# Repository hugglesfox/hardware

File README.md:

# Hardware

Random hardware design projects I have done. They probably don't work.

## Contents

- [obd2-pihat](https://github.com/hugglesfox/hardware/tree/master/obd2-pihat): An OBD-II hat for the raspberry pi.
- [fibonacci](https://github.com/hugglesfox/hardware/tree/master/fibonacci): A 4 bit fibonacci sequence calculator.

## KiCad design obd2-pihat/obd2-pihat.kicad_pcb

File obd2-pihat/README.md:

# OBD-II PiHAT

An OBD-II interface hat for the raspberry pi featuring the TI MCP2515 CAN
controller and a 12v to 5v power supply for backpowering the pi from the car
battery.

See the
[schematic](https://github.com/hugglesfox/hardware/blob/master/obd2-pihat/schematic.pdf)
for more details.

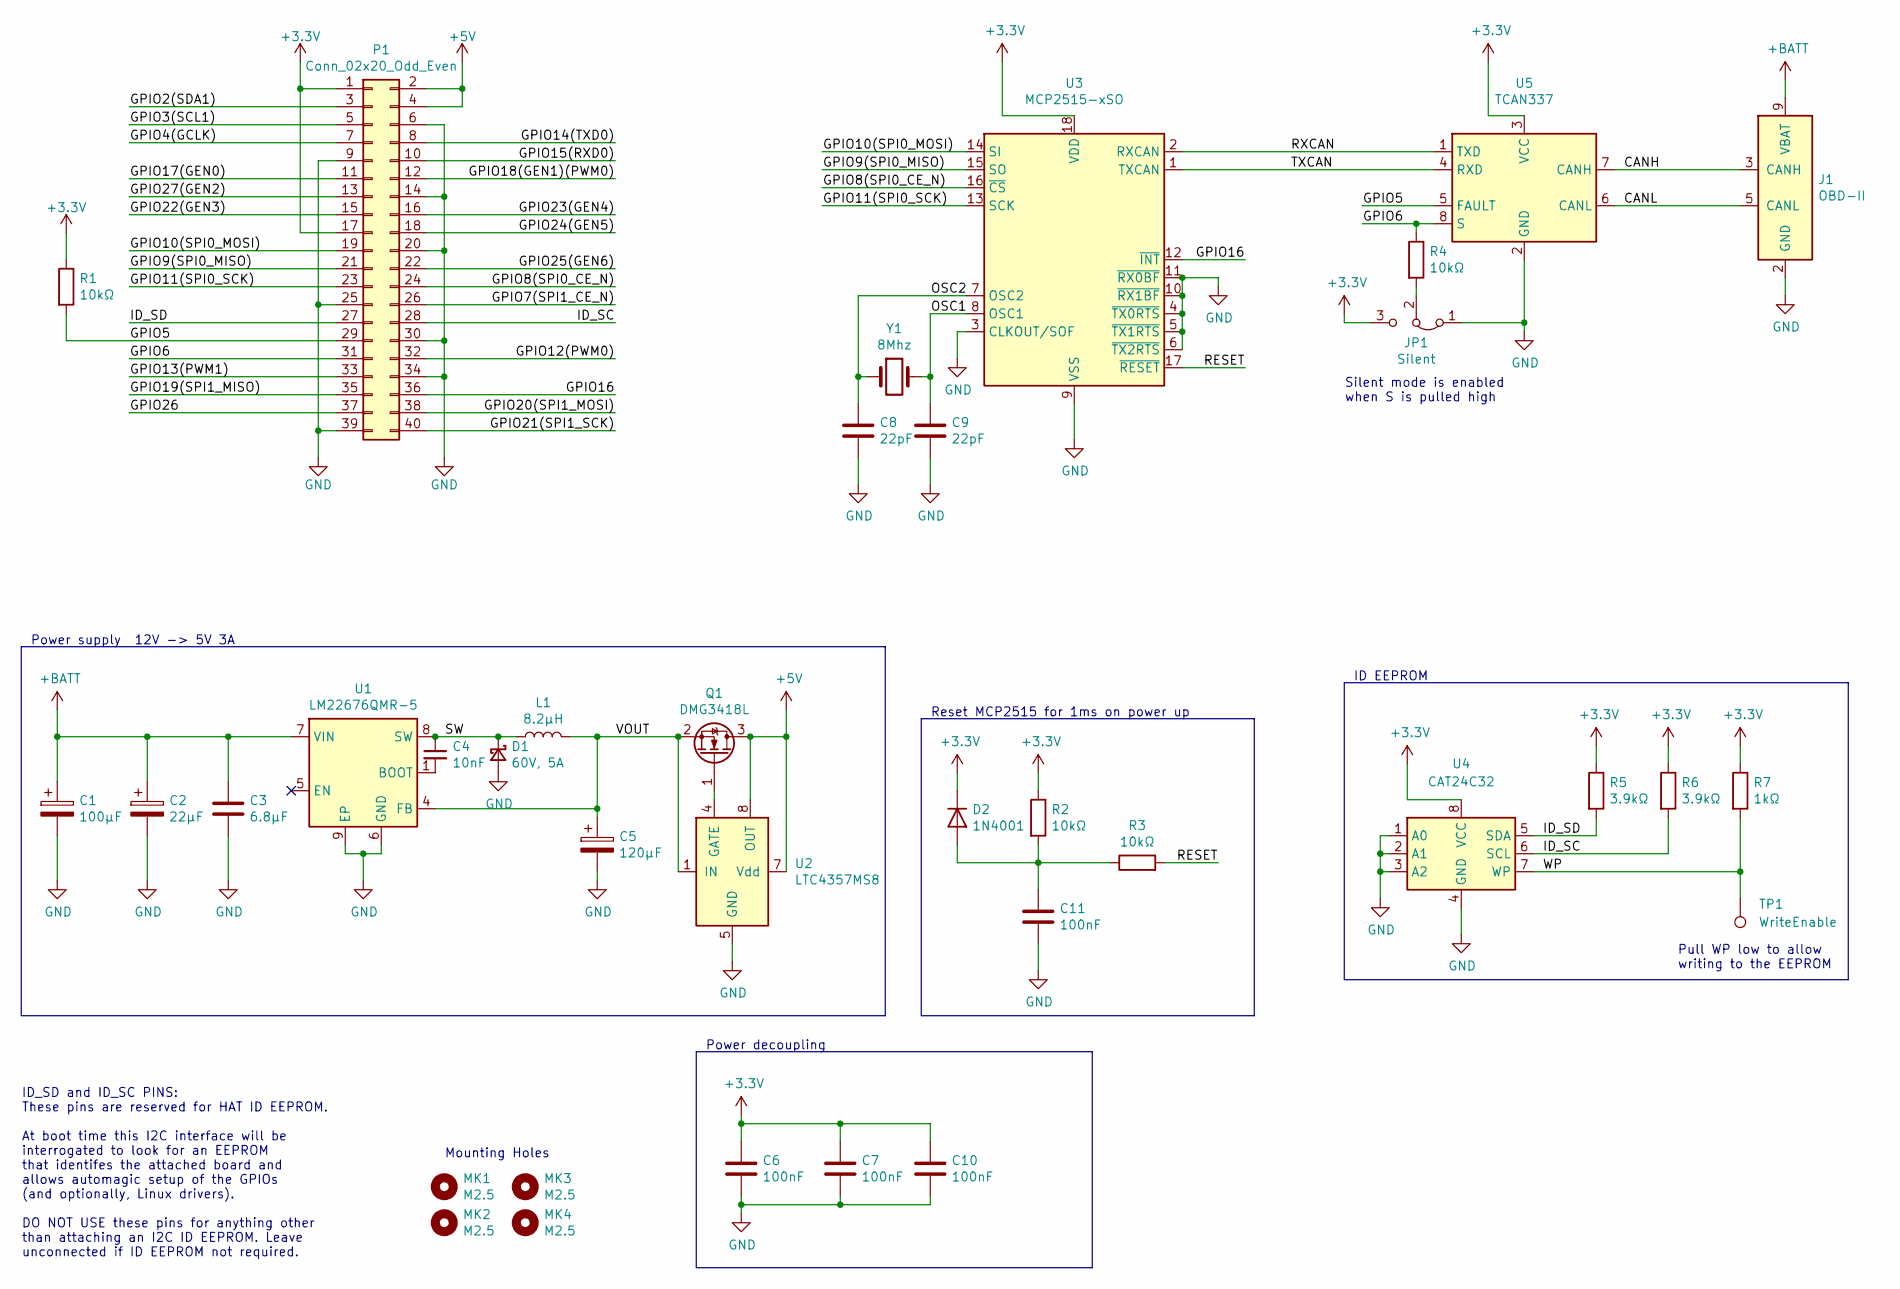
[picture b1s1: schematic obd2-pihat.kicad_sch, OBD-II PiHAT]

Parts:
C1: 100μF; CP_Elec_5x5.4
C2: 22μF; CP_Elec_4x5.4
C3: 6.8μF; C_0805_2012Metric_Pad1.18x1.45mm_HandSolder
C4: 10nF; C_0805_2012Metric_Pad1.18x1.45mm_HandSolder
C5: 120μF; CP_Elec_5x5.9
C6, C7, C10, C11: 100nF; C_0805_2012Metric_Pad1.18x1.45mm_HandSolder
C8, C9: 22pF; C_0805_2012Metric_Pad1.18x1.45mm_HandSolder
D1: 60V, 5A; D_SOD-128
D2: 1N4001; D_DO-41_SOD81_P10.16mm_Horizontal
J1: OBD-II; DSUB-9_Female_Horizontal_P2.77x2.84mm_EdgePinOffset4.94mm_H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
JP1: Silent; PinHeader_1x03_P2.54mm_Vertical
L1: 8.2μH; L_Vishay_IHLP-2525
MK1, MK2, MK3, MK4: M2.5; MountingHole_2.7mm_M2.5
P1: Conn_02x20_Odd_Even; PinSocket_2x20_P2.54mm_Vertical
Q1: DMG3418L; SOT-23
R1, R2, R3, R4: 10kΩ; R_0805_2012Metric_Pad1.20x1.40mm_HandSolder
R5, R6: 3.9kΩ; R_0805_2012Metric_Pad1.20x1.40mm_HandSolder
R7: 1kΩ; R_0805_2012Metric_Pad1.20x1.40mm_HandSolder
TP1: WriteEnable; TestPoint_Pad_D2.0mm
U1: LM22676QMR-5; TI_SO-PowerPAD-8_ThermalVias
U2: LTC4357MS8; MSOP-8_3x3mm_P0.65mm
U3: MCP2515-xSO; SOIC-18W_7.5x11.6mm_P1.27mm
U4: CAT24C32; SOIC-8_3.9x4.9mm_P1.27mm
U5: TCAN337; SOIC-8_3.9x4.9mm_P1.27mm
Y1: 8Mhz; Crystal_SMD_HC49-SD_HandSoldering

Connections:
+3V3: C6.1, C7.1, C10.1, D2.1 (K), JP1.3 (B), P1.1, P1.17, R1.1, R2.1, R5.1, R6.1, R7.1, U3.18 (VDD), U4.8 (VCC), U5.3 (VCC)
+5V: P1.2, P1.4, Q1.3 (D), U2.7 (Vdd), U2.8 (OUT)
+BATT: C1.1, C2.1, C3.1, J1.9 (VBAT), U1.7 (VIN)
/CANH: J1.3 (CANH), U5.7 (CANH)
/CANL: J1.5 (CANL), U5.6 (CANL)
/GPIO2(SDA1): P1.3
/GPIO3(SCL1): P1.5
/GPIO4(GCLK): P1.7
/GPIO5: P1.29, R1.2, U5.5 (FAULT)
/GPIO6: P1.31, R4.1, U5.8 (S)
/GPIO7(SPI1_CE_N): P1.26
/GPIO8(SPI0_CE_N): P1.24, U3.16 (~CS)
/GPIO9(SPI0_MISO): P1.21, U3.15 (SO)
/GPIO10(SPI0_MOSI): P1.19, U3.14 (SI)
/GPIO11(SPI0_SCK): P1.23, U3.13 (SCK)
/GPIO12(PWM0): P1.32
/GPIO13(PWM1): P1.33
/GPIO14(TXD0): P1.8
/GPIO15(RXD0): P1.10
/GPIO16: P1.36, U3.12 (~INT)
/GPIO17(GEN0): P1.11
/GPIO18(GEN1)(PWM0): P1.12
/GPIO19(SPI1_MISO): P1.35
/GPIO20(SPI1_MOSI): P1.38
/GPIO21(SPI1_SCK): P1.40
/GPIO22(GEN3): P1.15
/GPIO23(GEN4): P1.16
/GPIO24(GEN5): P1.18
/GPIO25(GEN6): P1.22
/GPIO26: P1.37
/GPIO27(GEN2): P1.13
/ID_SC: P1.28, R6.2, U4.6 (SCL)
/ID_SD: P1.27, R5.2, U4.5 (SDA)
/OSC1: C9.1, U3.8 (OSC1), Y1.2
/OSC2: C8.1, U3.7 (OSC2), Y1.1
/RESET: R3.2, U3.17 (~RESET)
/RXCAN: U3.2 (RXCAN), U5.1 (TXD)
/SW: C4.1, D1.1 (K), L1.1, U1.8 (SW)
/TXCAN: U3.1 (TXCAN), U5.4 (RXD)
/VOUT: C5.1, L1.2, Q1.2 (S), U1.4 (FB), U2.1 (IN)
/WP: R7.2, TP1.1, U4.7 (WP)
GND: C1.2, C2.2, C3.2, C5.2, C6.2, C7.2, C8.2, C9.2, C10.2, C11.2, D1.2 (A), J1.2 (GND), JP1.1 (A), P1.6, P1.9, P1.14, P1.20, P1.25, P1.30, P1.34, P1.39, U1.6 (GND), U1.9 (EP), U2.5 (GND), U3.3 (CLKOUT/SOF), U3.4 (~TX0RTS), U3.5 (~TX1RTS), U3.6 (~TX2RTS), U3.9 (VSS), U3.10 (~RX1BF), U3.11 (~RX0BF), U4.1 (A0), U4.2 (A1), U4.3 (A2), U4.4 (GND), U5.2 (GND)
unnamed: C4.2, U1.1 (BOOT)
unnamed: C11.1, D2.2 (A), R2.2, R3.1
unnamed: JP1.2 (C), R4.2
unnamed: Q1.1 (G), U2.4 (GATE)

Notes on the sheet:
Mounting Holes
ID_SD and ID_SC PINS: These pins are reserved for HAT ID EEPROM. At boot time this I2C interface will be interrogated to look for an EEPROM that identifes the attached board and allows automagic setup of the GPIOs (and optionally, Linux drivers). DO NOT USE these pins for anything other than attach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
Reset MCP2515 for 1ms on power up
Power supply 12V -> 5V 3A
Silent mode is enabled when S is pulled high
ID EEPROM
Pull WP low to allow writing to the EEPROM
Power decoupling

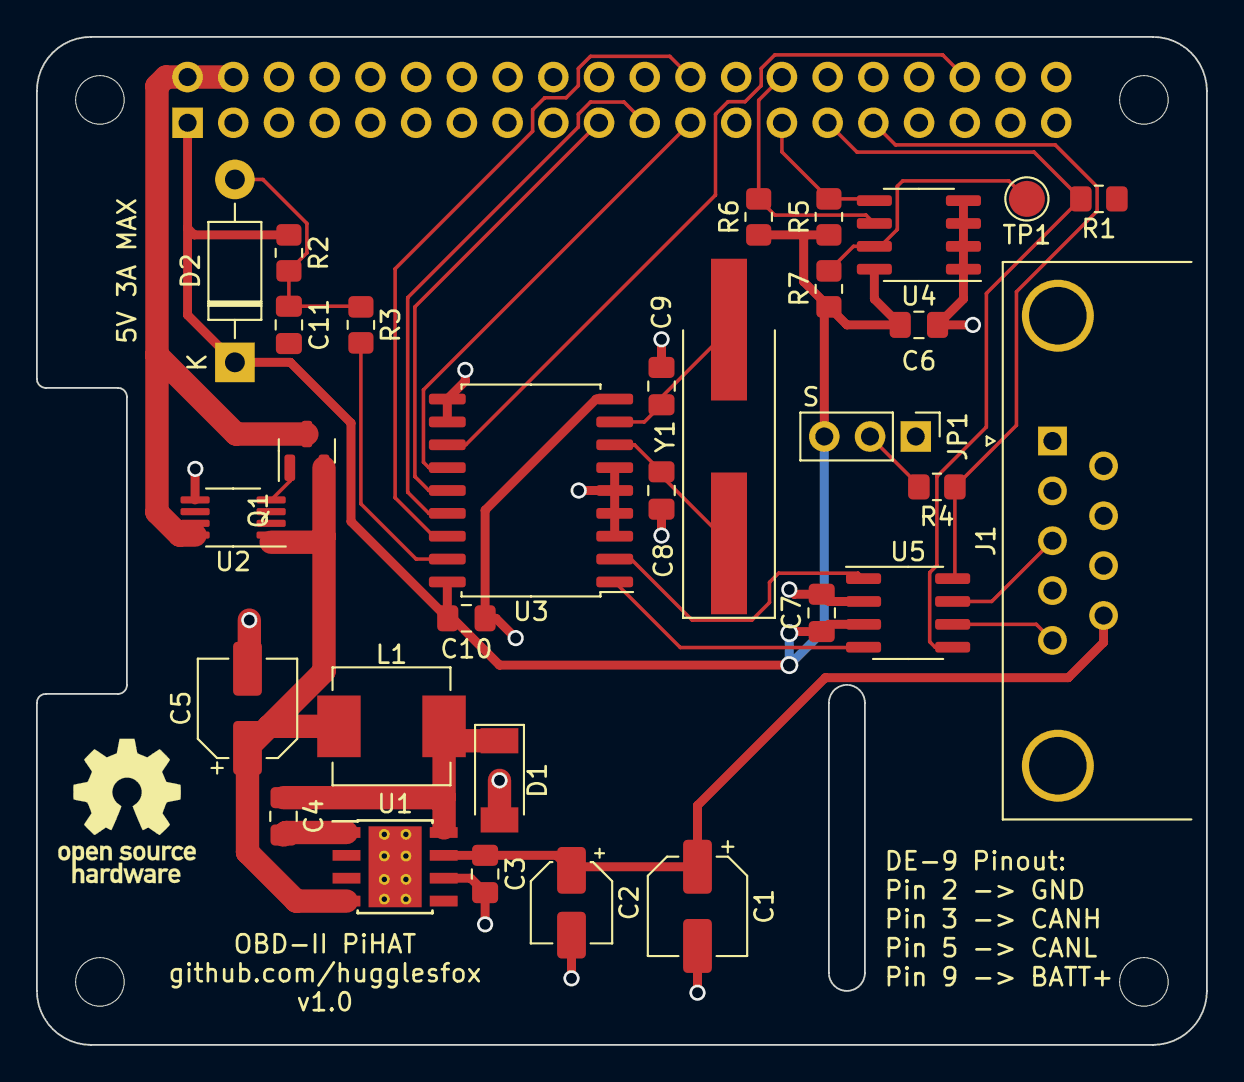
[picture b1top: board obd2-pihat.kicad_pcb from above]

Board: 2 copper layers, 65.0 x 56.0 mm, 36 parts (1 on the bottom side), 27 nets.

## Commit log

2020-08-25 Add fibonacci
2021-12-01 Add kicad 6 backups to gitignore
2021-12-01 Add obd2-pihat
2021-12-01 Add basic documentation for obd2-pihat
